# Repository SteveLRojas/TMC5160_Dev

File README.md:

# TMC5160_Dev
Development board for TMC5160 and TMC5160A. This board is designed to fit the Alchemy board.

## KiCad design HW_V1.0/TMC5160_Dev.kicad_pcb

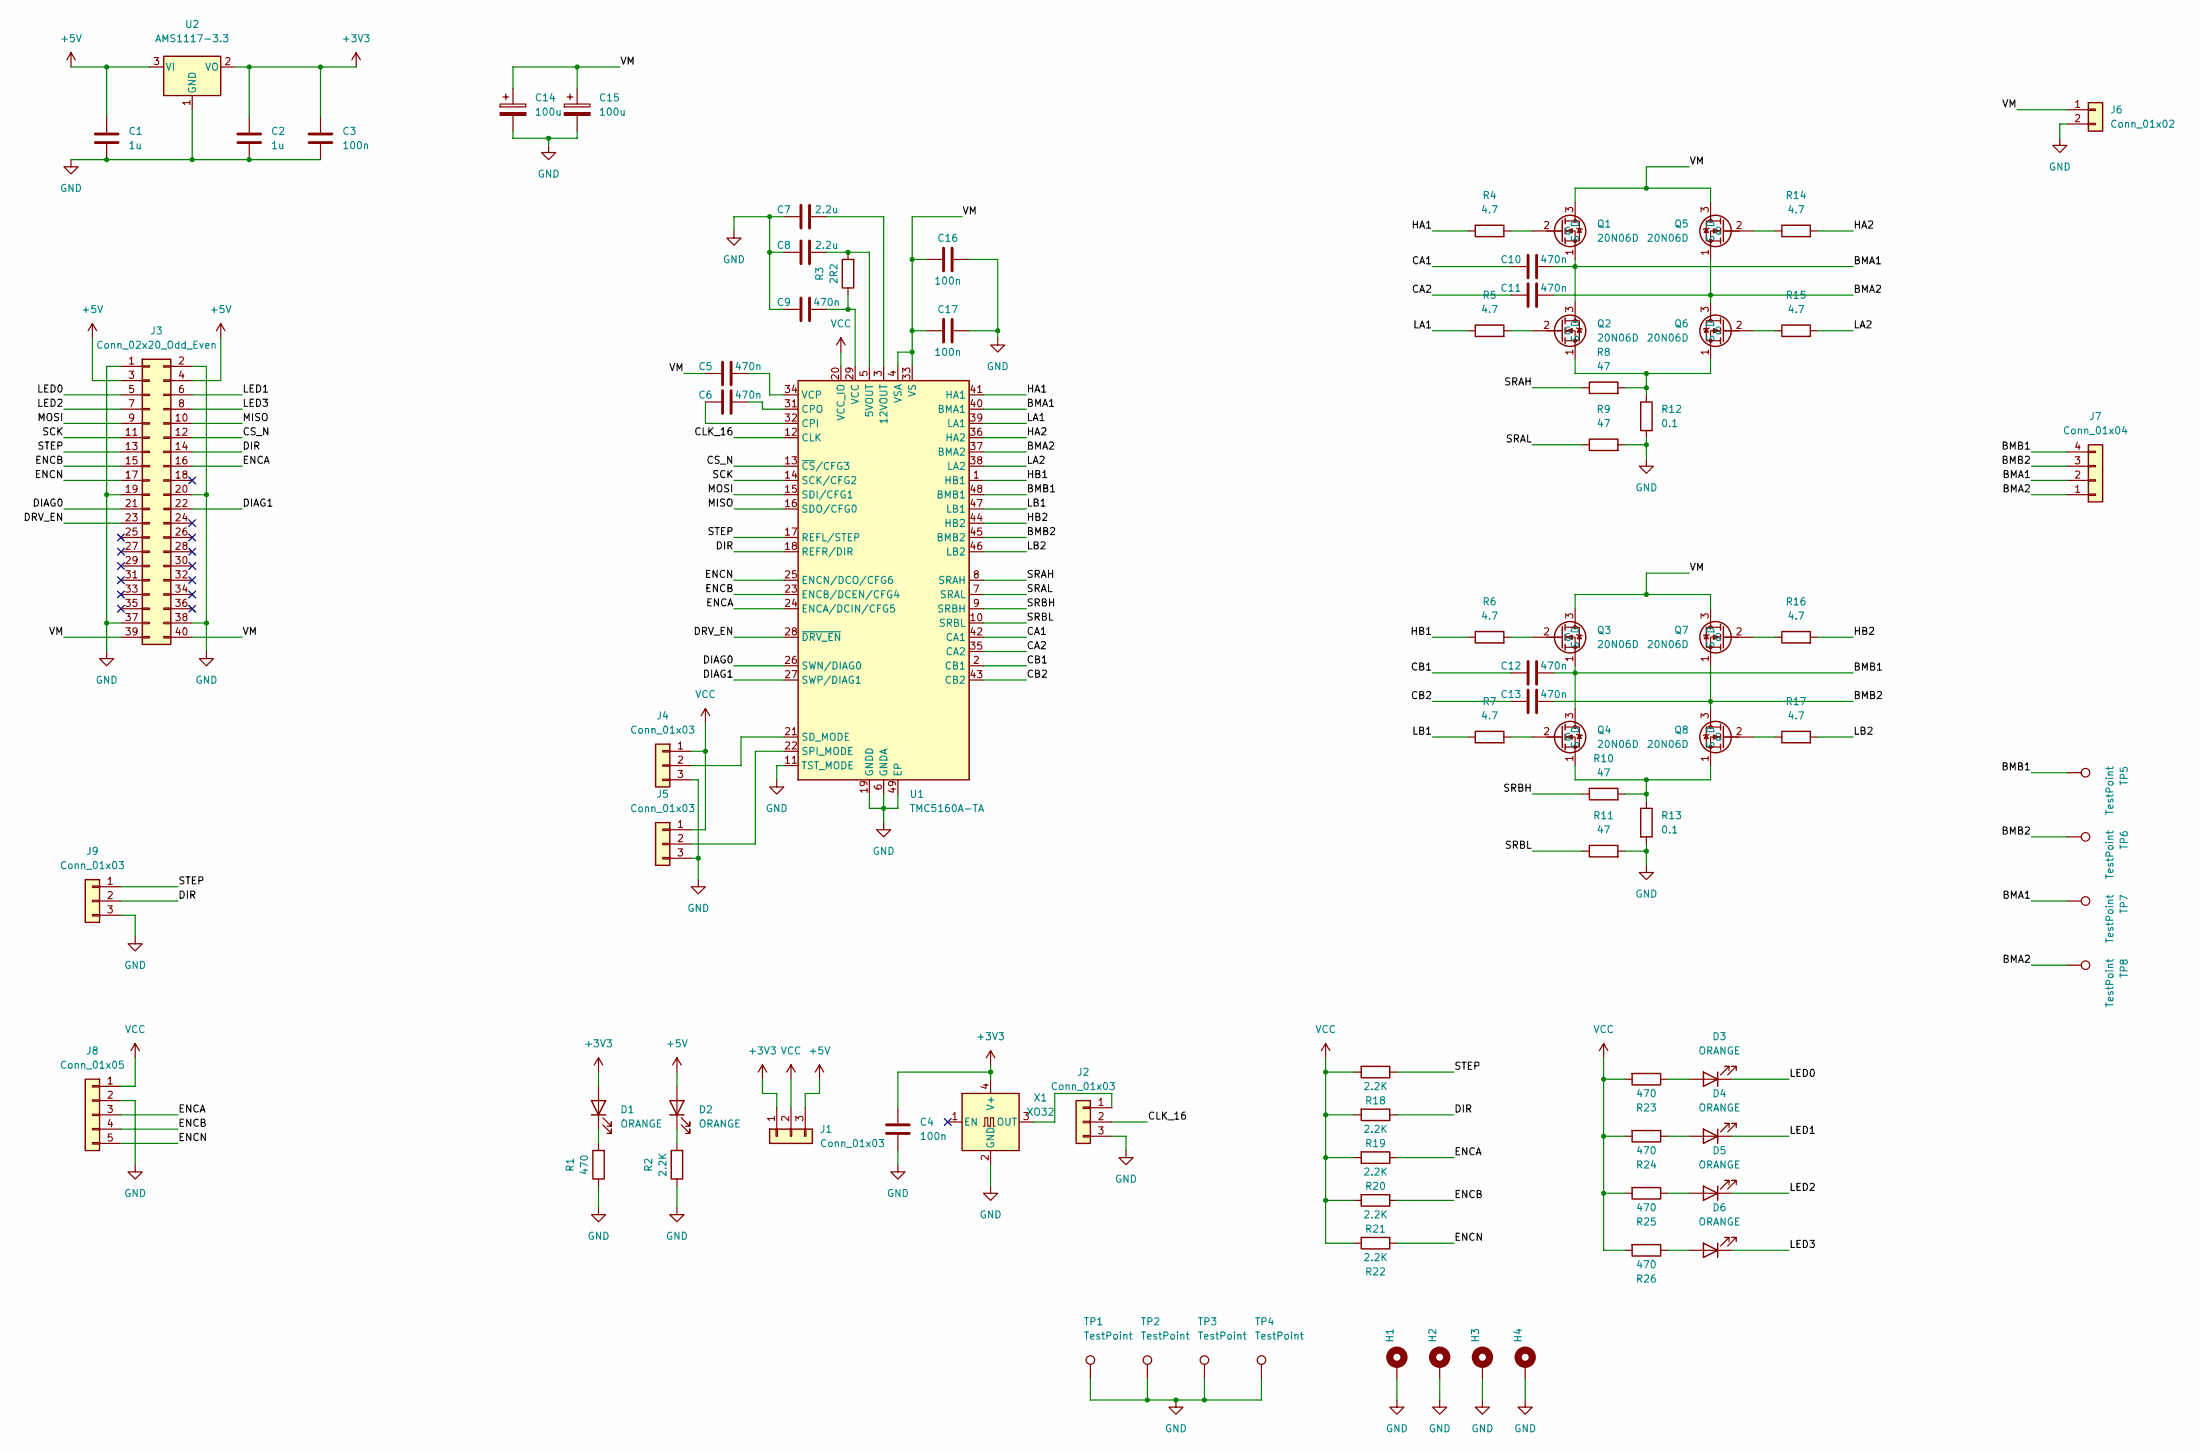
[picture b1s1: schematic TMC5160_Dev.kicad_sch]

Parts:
C1, C2: 1u; C_0805_2012Metric
C3, C4, C16, C17: 100n; C_0805_2012Metric
C5, C6, C9, C10, C11, C12, C13: 470n; C_0805_2012Metric
C7, C8: 2.2u; C_0805_2012Metric
C14, C15: 100u; CP_Radial_D10.0mm_P5.00mm
D1, D2, D3, D4, D5, D6: ORANGE; LED_0805_2012Metric
H1, H2, H3, H4: MountingHole_Pad; MountingHole_3.2mm_M3_Pad
J1, J2, J4, J5, J9: Conn_01x03; PinHeader_1x03_P2.54mm_Vertical
J3: Conn_02x20_Odd_Even; PinSocket_2x20_P2.54mm_Horizontal
J6: Conn_01x02; PhoenixContact_MSTBA_2,5_2-G-5,08_1x02_P5.08mm_Horizontal
J7: Conn_01x04; PhoenixContact_MC_1,5_4-G-3.81_1x04_P3.81mm_Horizontal
J8: Conn_01x05; PinHeader_1x05_P2.54mm_Vertical
Q1, Q2, Q3, Q4, Q5, Q6, Q7, Q8: 20N06D; 20N60D
R1, R23, R24, R25, R26: 470; R_0805_2012Metric
R2, R18, R19, R20, R21, R22: 2.2K; R_0805_2012Metric
R3: 2R2; R_0805_2012Metric
R4, R5, R6, R7, R14, R15, R16, R17: 4.7; R_0805_2012Metric
R8, R9, R10, R11: 47; R_0805_2012Metric
R12, R13: 0.1; R_1210_3225Metric
TP1, TP2, TP3, TP4, TP5, TP6, TP7, TP8: TestPoint; TestPoint_Loop_D2.50mm_Drill1.0mm
U1: TMC5160A-TA; TQFP-48-1EP_7x7mm_P0.5mm_EP5x5mm_ThermalVias
U2: AMS1117-3.3; SOT-223-3_TabPin2
X1: XO32; Oscillator_SMD_EuroQuartz_XO32-4Pin_3.2x2.5mm

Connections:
+3V3: C2.1, C3.1, C4.1, D1.2 (A), J1.1, U2.2 (VO), X1.4 (V+)
+5V: C1.1, D2.2 (A), J1.3, J3.3, J3.4, U2.3 (VI)
/BMA1: C10.2, J7.2, Q1.1 (S), Q2.3 (D), TP7.1, U1.40 (BMA1)
/BMA2: C11.2, J7.1, Q5.1 (S), Q6.3 (D), TP8.1, U1.37 (BMA2)
/BMB1: C12.2, J7.4, Q3.1 (S), Q4.3 (D), TP5.1, U1.48 (BMB1)
/BMB2: C13.2, J7.3, Q7.1 (S), Q8.3 (D), TP6.1, U1.45 (BMB2)
/CA1: C10.1, U1.42 (CA1)
/CA2: C11.1, U1.35 (CA2)
/CB1: C12.1, U1.2 (CB1)
/CB2: C13.1, U1.43 (CB2)
/CLK_16: J2.2, U1.12 (CLK)
/CS_N: J3.12, U1.13 (~CS/CFG3)
/DIAG0: J3.21, U1.26 (SWN/DIAG0)
/DIAG1: J3.22, U1.27 (SWP/DIAG1)
/DIR: J3.14, J9.2, R19.1, U1.18 (REFR/DIR)
/DRV_EN: J3.23, U1.28 (~DRV_EN)
/ENCA: J3.16, J8.3, R20.1, U1.24 (ENCA/DCIN/CFG5)
/ENCB: J3.15, J8.4, R21.1, U1.23 (ENCB/DCEN/CFG4)
/ENCN: J3.17, J8.5, R22.1, U1.25 (ENCN/DCO/CFG6)
/HA1: R4.1, U1.41 (HA1)
/HA2: R14.2, U1.36 (HA2)
/HB1: R6.1, U1.1 (HB1)
/HB2: R16.2, U1.44 (HB2)
/LA1: R5.1, U1.39 (LA1)
/LA2: R15.2, U1.38 (LA2)
/LB1: R7.1, U1.47 (LB1)
/LB2: R17.2, U1.46 (LB2)
/LED0: D3.1 (K), J3.5
/LED1: D4.1 (K), J3.6
/LED2: D5.1 (K), J3.7
/LED3: D6.1 (K), J3.8
/MISO: J3.10, U1.16 (SDO/CFG0)
/MOSI: J3.9, U1.15 (SDI/CFG1)
/SCK: J3.11, U1.14 (SCK/CFG2)
/SRAH: R8.1, U1.8 (SRAH)
/SRAL: R9.1, U1.7 (SRAL)
/SRBH: R10.1, U1.9 (SRBH)
/SRBL: R11.1, U1.10 (SRBL)
/STEP: J3.13, J9.1, R18.1, U1.17 (REFL/STEP)
/VM: C5.1, C14.1, C15.1, C16.1, C17.1, J3.39, J3.40, J6.1, Q1.3 (D), Q3.3 (D), Q5.3 (D), Q7.3 (D), U1.4 (VSA), U1.33 (VS)
GND: C1.2, C2.2, C3.2, C4.2, C7.1, C8.1, C9.1, C14.2, C15.2, C16.2, C17.2, H1.1, H2.1, H3.1, H4.1, J2.3, J3.1, J3.2, J3.19, J3.20, J3.37, J3.38, J4.3, J5.3, J6.2, J8.2, J9.3, R1.1, R2.1, R9.2, R11.2, R12.2, R13.2, TP1.1, TP2.1, TP3.1, TP4.1, U1.6 (GNDA), U1.11 (TST_MODE), U1.19 (GNDD), U1.30 (GNDD), U1.49 (EP), U2.1 (GND), X1.2 (GND)
unnamed: C5.2, U1.34 (VCP)
unnamed: C6.1, U1.32 (CPI)
unnamed: C6.2, U1.31 (CPO)
unnamed: C7.2, U1.3 (12VOUT)
unnamed: C8.2, R3.2, U1.5 (5VOUT)
unnamed: C9.2, R3.1, U1.29 (VCC)
unnamed: D1.1 (K), R1.2
unnamed: D2.1 (K), R2.2
unnamed: D3.2 (A), R23.1
unnamed: D4.2 (A), R24.1
unnamed: D5.2 (A), R25.1
unnamed: D6.2 (A), R26.1
unnamed: J2.1, X1.3 (OUT)
unnamed: J4.2, U1.21 (SD_MODE)
unnamed: J5.2, U1.22 (SPI_MODE)
unnamed: Q1.2 (G), R4.2
unnamed: Q2.1 (S), Q6.1 (S), R8.2, R12.1
unnamed: Q2.2 (G), R5.2
unnamed: Q3.2 (G), R6.2
unnamed: Q4.1 (S), Q8.1 (S), R10.2, R13.1
unnamed: Q4.2 (G), R7.2
unnamed: Q5.2 (G), R14.1
unnamed: Q6.2 (G), R15.1
unnamed: Q7.2 (G), R16.1
unnamed: Q8.2 (G), R17.1
VCC: J1.2, J4.1, J5.1, J8.1, R18.2, R19.2, R20.2, R21.2, R22.2, R23.2, R24.2, R25.2, R26.2, U1.20 (VCC_IO)

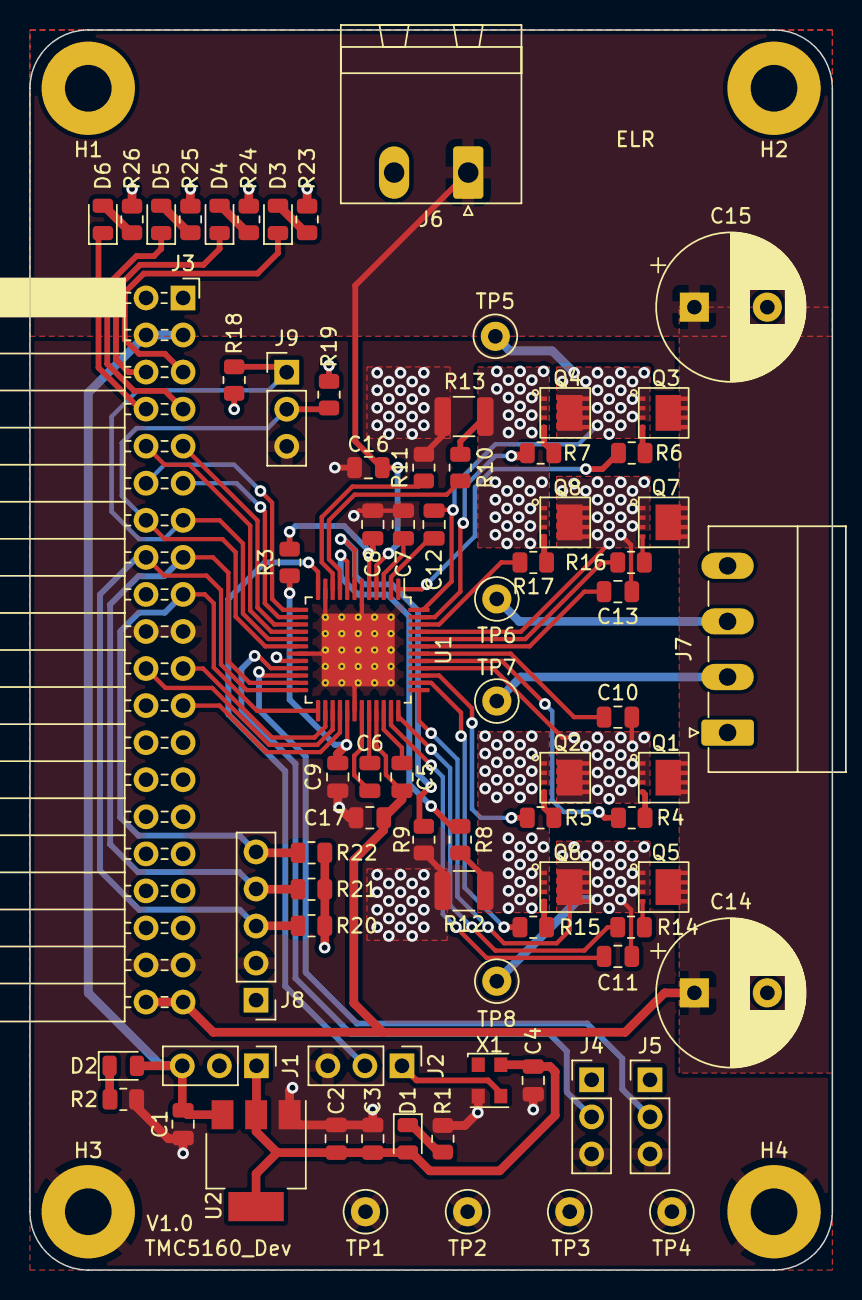
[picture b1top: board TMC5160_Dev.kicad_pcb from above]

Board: 4 copper layers, 55.0 x 85.0 mm, 81 parts (0 on the bottom side), 67 nets.

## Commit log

2025-05-10 Added design files
